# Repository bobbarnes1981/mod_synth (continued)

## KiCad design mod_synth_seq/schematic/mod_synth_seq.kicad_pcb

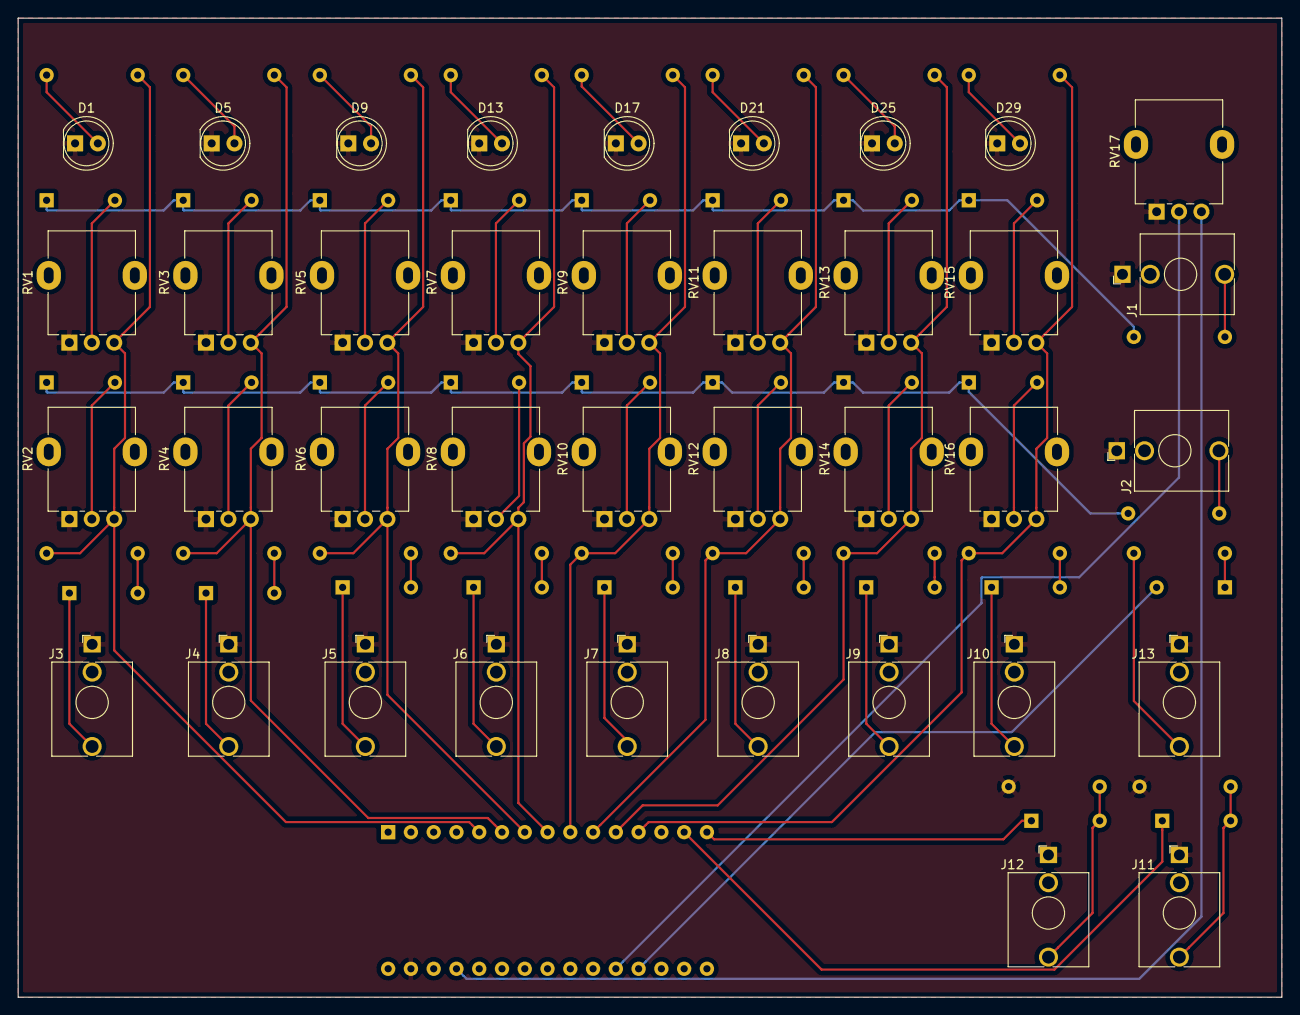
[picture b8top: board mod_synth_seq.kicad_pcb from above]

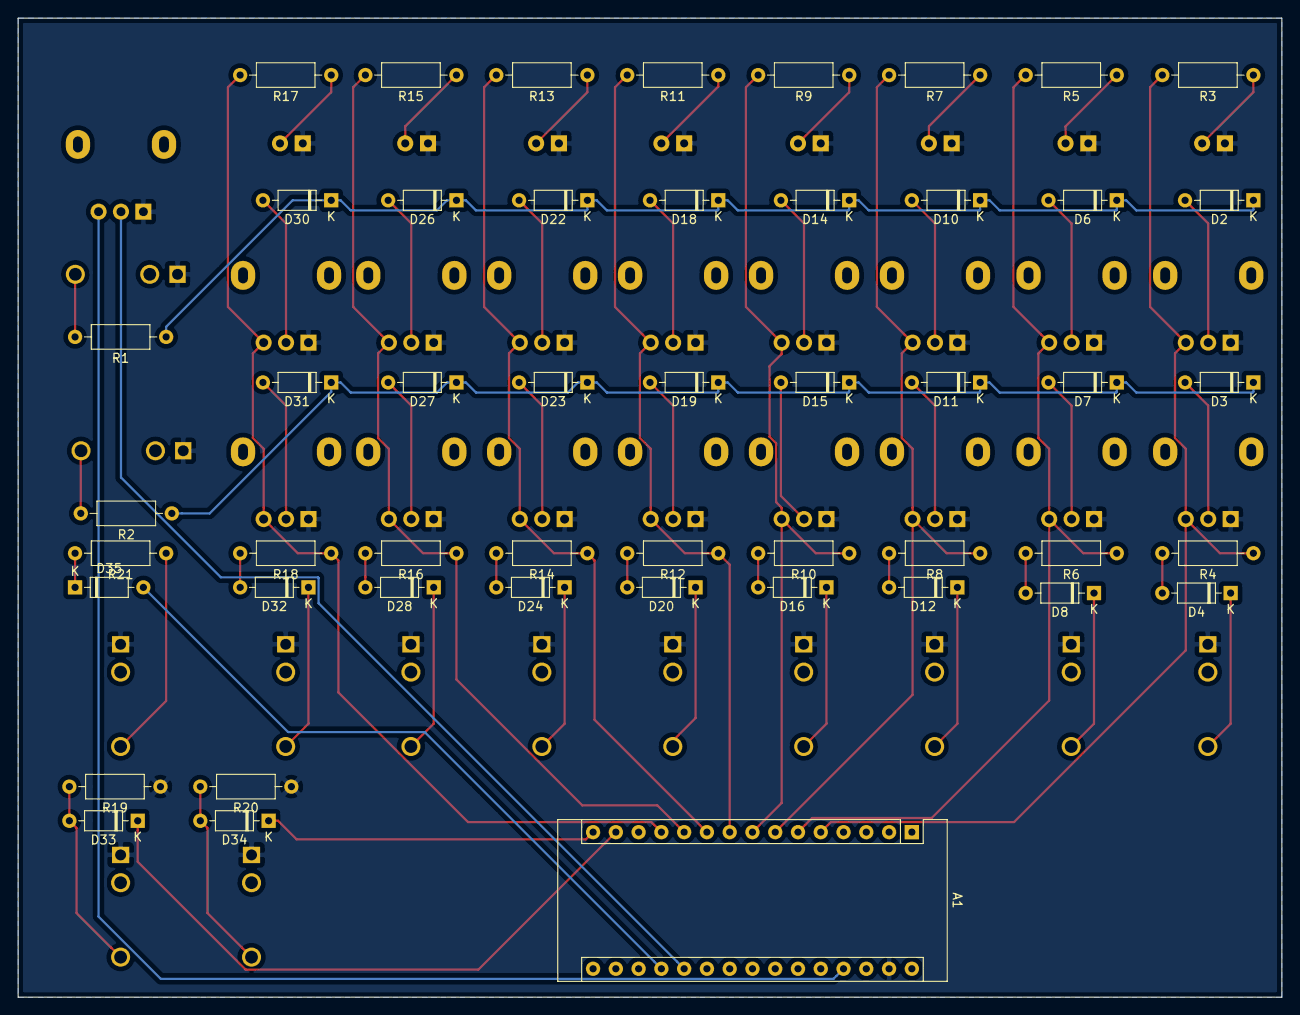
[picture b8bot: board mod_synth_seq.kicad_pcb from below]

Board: 2 copper layers, 141.0 x 109.2 mm, 87 parts (49 on the bottom side), 62 nets.

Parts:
A1: Arduino_Nano_v3.x; Arduino_Nano
D1, D5, D9, D13, D17, D21, D25, D29: LED; LED_D5.0mm
D2, D3, D4, D6, D7, D8, D10, D11, D12, D14, D15, D16, D18, D19, D20, D22, D23, D24, D26, D27, D28, D30, D31, D32, D33, D34, D35: 1N4148; D_DO-35_SOD27_P7.62mm_Horizontal
J1: CV1; Jack_3.5mm_QingPu_WQP-PJ398SM_Vertical_CircularHoles
J2: CV2; Jack_3.5mm_QingPu_WQP-PJ398SM_Vertical_CircularHoles
J3: Step 1 Gate; Jack_3.5mm_QingPu_WQP-PJ398SM_Vertical_CircularHoles
J4: Step 2 Gate; Jack_3.5mm_QingPu_WQP-PJ398SM_Vertical_CircularHoles
J5: Step 3 Gate; Jack_3.5mm_QingPu_WQP-PJ398SM_Vertical_CircularHoles
J6: Step 4 Gate; Jack_3.5mm_QingPu_WQP-PJ398SM_Vertical_CircularHoles
J7: Step 5 Gate; Jack_3.5mm_QingPu_WQP-PJ398SM_Vertical_CircularHoles
J8: Step 6 Gate; Jack_3.5mm_QingPu_WQP-PJ398SM_Vertical_CircularHoles
J9: Step 7 Gate; Jack_3.5mm_QingPu_WQP-PJ398SM_Vertical_CircularHoles
J10: Step 8 Gate; Jack_3.5mm_QingPu_WQP-PJ398SM_Vertical_CircularHoles
J11: Reset; Jack_3.5mm_QingPu_WQP-PJ398SM_Vertical_CircularHoles
J12: Clock; Jack_3.5mm_QingPu_WQP-PJ398SM_Vertical_CircularHoles
J13: Gate Out; Jack_3.5mm_QingPu_WQP-PJ398SM_Vertical_CircularHoles
R1, R2, R3, R4, R5, R6, R7, R8, R9, R10, R11, R12, R13, R14, R15, R16, R17, R18, R21: 1k; R_Axial_DIN0207_L6.3mm_D2.5mm_P10.16mm_Horizontal
R19, R20: 10k; R_Axial_DIN0207_L6.3mm_D2.5mm_P10.16mm_Horizontal
RV1, RV2, RV3, RV4, RV5, RV6, RV7, RV8, RV9, RV10, RV11, RV12, RV13, RV14, RV15, RV16, RV17: 100k Lin; Potentiometer_Alpha_RD901F-40-00D_Single_Vertical

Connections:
+5V: A1.27, RV17.3
GND: A1.29, D1.1, D5.1, D9.1, D13.1, D17.1, D21.1, D25.1, D29.1, J1.S, J2.S, J3.S, J4.S, J5.S, J6.S, J7.S, J8.S, J9.S, J10.S, J11.S, J12.S, J13.S, R19.1, R20.1, RV1.1, RV2.1, RV3.1, RV4.1, RV5.1, RV6.1, RV7.1, RV8.1, RV9.1, RV10.1, RV11.1, RV12.1, RV13.1, RV14.1, RV15.1, RV16.1, RV17.1
unnamed: A1.5, R3.2, R4.1, RV1.3, RV2.3
unnamed: A1.6, R5.2, R6.1, RV3.3, RV4.3
unnamed: A1.7, R7.2, R8.1, RV5.3, RV6.3
unnamed: A1.8, R9.2, R10.1, RV7.3, RV8.3
unnamed: A1.9, R11.2, R12.1, RV9.3, RV10.3
unnamed: A1.10, R13.2, R14.1, RV11.3, RV12.3
unnamed: A1.11, R15.2, R16.1, RV13.3, RV14.3
unnamed: A1.12, R17.2, R18.1, RV15.3, RV16.3
unnamed: A1.14, D33.1
unnamed: A1.15, D34.1
unnamed: A1.19, D35.2
unnamed: A1.20, RV17.2
unnamed: D1.2, R3.1
unnamed: D2.2, RV1.2
unnamed: D3.2, RV2.2
unnamed: D4.1, J3.T
unnamed: D4.2, R4.2
unnamed: D5.2, R5.1
unnamed: D6.2, RV3.2
unnamed: D7.2, RV4.2
unnamed: D8.1, J4.T
unnamed: D8.2, R6.2
unnamed: D9.2, R7.1
unnamed: D2.1, D6.1, D10.1, D14.1, D18.1, D22.1, D26.1, D30.1, R1.1
unnamed: D10.2, RV5.2
unnamed: D3.1, D7.1, D11.1, D15.1, D19.1, D23.1, D27.1, D31.1, R2.1
unnamed: D11.2, RV6.2
unnamed: D12.1, J5.T
unnamed: D12.2, R8.2
unnamed: D13.2, R9.1
unnamed: D14.2, RV7.2
unnamed: D15.2, RV8.2
unnamed: D16.1, J6.T
unnamed: D16.2, R10.2
unnamed: D17.2, R11.1
unnamed: D18.2, RV9.2
unnamed: D19.2, RV10.2
unnamed: D20.1, J7.T
unnamed: D20.2, R12.2
unnamed: D21.2, R13.1
unnamed: D22.2, RV11.2
unnamed: D23.2, RV12.2
unnamed: D24.1, J8.T
unnamed: D24.2, R14.2
unnamed: D25.2, R15.1
unnamed: D26.2, RV13.2
unnamed: D27.2, RV14.2
unnamed: D28.1, J9.T
unnamed: D28.2, R16.2
unnamed: D29.2, R17.1
unnamed: D30.2, RV15.2
unnamed: D31.2, RV16.2
unnamed: D32.1, J10.T
unnamed: D32.2, R18.2
unnamed: D33.2, J11.T, R19.2
unnamed: D34.2, J12.T, R20.2
unnamed: D35.1, R21.2
unnamed: J1.T, R1.2
unnamed: J2.T, R2.2
unnamed: J13.T, R21.1
